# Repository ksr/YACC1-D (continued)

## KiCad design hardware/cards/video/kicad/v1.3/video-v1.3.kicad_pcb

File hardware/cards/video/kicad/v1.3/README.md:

# video-v1.3 — KiCad design for the video card

**Superseded by `../v2.0/` (2026-10-22), which builds on it; kept as the DOTS-jumper design. Not ordered.**

(Was the master from 2026-10-22.) v1.3 is `../v1.2/` (the bench state of 2026-10-21) with one
jumper that chooses **6 or 8 dots a character**, and a new board: **4 layers, routed from scratch** - In1.Cu a solid GND
plane, In2.Cu a solid VCC plane, every signal routed anew, GND and VCC never routed (every power pin is a through-hole
pad on its plane). The outline, the bus connector X1 and the placement are v1.2's; the parts v1.3 adds sit beside IC28.
`tools/eagle_to_kicad_all.py` never writes here (`MASTER` marker file). `./build.sh` rebuilds the board and every report
and checks them (needs KiCad 10 and Freerouting 1.9).

## The two modes

One 12 MHz crystal (Q2, SV4 on 1-2) serves both:

| DOTS jumper (JP2) | IC28 divides by | character clock | screen | 6845 R0..R9 | dots across | EPROM time a character |
|---|---|---|---|---|---|---|
| open (R15 pulls DOTS high) | 6 | 2.0 MHz | **80 x 24** | 126, 80, 98, 10, 31, 6, 24, 27, 0, 7 | 480 | 500 ns |
| fitted (DOTS to GND) | 8 | 1.5 MHz | **64 x 24** | 94, 64, 75, 8, 31, 6, 24, 27, 0, 7 | 512 | 667 ns |

Both 15.75 kHz / 60 Hz. The 64 x 24 table is the one proven on a TV-rate monitor on 2026-10-21 (9 MHz / 6 = the same
1.5 MHz); the 80 x 24 table is centred in that monitor's measured visible window (about 10.3-58.3 us after the sync
starts: the text runs 14.5-54.5 us). `python3 tools/vidsim.py testcard --card v1.3 --dots 6|8 --png card.png` draws
each mode; `vidsim.py chargen --card v1.3` writes the EPROM (`firmware/video/chargen-v13.bin`).

## Changes since v1.2 (schematic)

| # | Change | Pins |
|---|---|---|
| 1 | **IC28 (74163) divides by 16 - P, loading P on its carry** | -CLR (1) to VCC; data A (3) GND, B (4) **DOTS**, C (5) GND, D (6) VCC: P = 8 (/8) or 10 (/6); -LOAD (9) = CHARCLOCK; RCO (15) = net `RCO`; QA (14) unconnected; ENT/ENP (10, 7) stay on N$73 (R10). CRTCCLOCK stays QC (12) -> IC17 21 |
| 2 | **CHARCLOCK = NOT RCO** | IC19/C both inputs (9, 10) on `RCO` (were QA and CRTCCLOCK): one dot low at count 15 in both modes, the same pulse the 74LS166 load and IC22/IC23 get in v1.2 |
| 3 | **DOTS jumper JP2** (2-pin header, silk "DOTS: ON=8") + **R15 4.7k** pull-up | JP2 1 = DOTS, 2 = GND; R15 VCC - DOTS. Fitted = 8 dots, open = 6 dots |
| 4 | **Font select: DOTS on EPROM A10** | IC25 pin 19 (was GND): the 8-dot font at $000, the 6-dot font at $400; A9, A11 stay GND |
| 5 | **DOTS readable at `$D801` bit 0** | latch IC2 1D (pin 3) on DOTS (was JP1 pin 1, now unconnected): 1 = 6 dots, 0 = 8. IC2 LE (pin 11) to VCC (was JP1 pin 13, which floated): the latch is transparent by design; JP1 pin 13 unconnected |
| 5a | **Card ID at `$D801` bit 2** (2026-10-22) | latch IC2 3D (pin 7) to GND (was JP1 pin 4, now unconnected, no-connect flag): bit 2 = 0 says "V1.3" to `ROM 2026-10-22` and later, which then reads DOTS on bit 0 for 80 x 24 or 64 x 24; the V1.0-V1.2 card reads bit 2 = 1 (a jumper on its JP1 3-4) and keeps its 11.0592 MHz table |
| 6 | **IC24 (74LS166) loads all eight bits** | A, B, C (2, 3, 4; were GND) to EPROM O0, O1, O2 (IC25 9, 10, 11) on nets `CG0..CG2`. In 6-dot mode the next load comes after 6 shifts, so only O7..O2 are seen |
| 7 | values, title | Q2 **12MHz**; IC25 **2732 (chargen-v13)**; silkscreen "YACC1 Video Card V1.3" |

Unchanged from v1.2: RS on ADDR1, LPSTB to GND, the R13 / R14 4.7k pull-ups, E without the one-shot (IC1 pin 2 on VCC).
Characters stay 8 scan lines tall in both modes (R9 = 7): taller ones need RA3 to the EPROM and would break the
proposed graphics overlay's 8-plane addressing (`BACKLOG.md`).

**The 6845's clock in 6-dot mode.** QC over counts 10..15 is low for 2 dots and high for 4: **167 ns low / 333 ns high**
at 12 MHz (8-dot mode: 333 / 333 ns). Motorola's MC6845 data sheet gives a minimum clock pulse width of 160 ns low and
200 ns high (**To verify:** from the data sheet as remembered - the tree's `docs/BYTE 6845.pdf` is a scan without the
timing table). 167 ns against 160 ns is a margin of only 7 ns. Fit a faster grade (MC68A45 / MC68B45, or an HD6845S) for
the 6-dot mode, or check the fitted part's sheet; 8-dot mode has ample margin. The ROM's support (read `$D801` bit 0 at
reset, pick 80 or 64 columns and the table) is the next step (`BACKLOG.md`, "Video v1.3").

**The EPROM in 6-dot mode** gets 500 ns a character; the MBM2732A is a 450 ns part: it works with little slack. A faster
part (a 2732A-25, or a 27C32/2764 at 250 ns with a socket adapter) removes the worry.

## The board

| | |
|---|---|
| Layers | 4, 1.6 mm (JLCPCB-style 4-layer): F.Cu signals, **In1.Cu GND plane**, **In2.Cu VCC plane**, B.Cu signals |
| Rules (`video-v1.3.kicad_dru`, the project's net classes) | as the memory card v2.0: signal tracks 0.25 mm, clearance 0.2 mm, vias 0.8 / 0.4 mm, copper to edge 0.5 mm; plane antipads 0.3 mm, thermal reliefs 0.4 mm gap / 0.5 mm spokes; class Power = GND, VCC: not routed |
| Outline, X1, placement | v1.2's (177.8 x 114.0 mm); **JP2** at (179.7, 116.6), pads horizontal, right of IC28; **R15** vertical at x = 185.4 (pads at y 113.0 / 120.62); the "DOTS: ON=8" label below JP2 |
| Route | Freerouting 1.9 on a 2-signal-layer copy (planes dropped, `-inc Power`), one run per DSN component order (seeds 0-7, in parallel), the best kept: **seed 7: 0 unrouted, 39 vias, 8.41 m of 0.25 mm track** (F.Cu 4.29 m, B.Cu 4.13 m; rebuilt 2026-10-22 with the card ID). The other seeds: 39-52 vias, seed 1 with 3 clearance findings |
| Planes | each one solid piece (GND 17,737 mm², VCC 17,724 mm² of the 20,270 mm² board; the rest antipads), plus a few 0.8 mm² slivers between X1's pins |

## Proof

- Schematic vs board (`tools/kicad/compare_netlists.py`): **MATCH, 115/115 nets** (116 before the card ID: N$13 is gone).
- DRC: **0 unconnected** (every GND/VCC pad reaches its net through its plane only: the planes connect), no clearance,
  short or dangling-track finding; the residue is v1.2's cosmetic set, unchanged by type and count: silk_over_copper
  199, silk_overlap 15, silk_edge_clearance 8, lib_footprint_mismatch 3, items_not_allowed 2 (X1's mounting holes in
  X1's own keepout), text_height 2. Schematic parity: footprint_symbol_mismatch 16 and net_conflict 29, the conversion's
  inherited value texts and its "unconnected-(...)" pins, as v1.2; the three net_conflict items v1.2 lacks are the pins
  v1.3 leaves unconnected (IC28 14, JP1 1, JP1 4, JP1 13), and v1.2's for IC28 15 and IC25 9-11 are gone (now used).
- ERC: endpoint_off_grid 35, isolated_pin_label 56, pin_to_pin 9 - v1.2's cosmetic set, unchanged.
- `gen_v13.py verify`: every change above checked pin by pin in the schematic netlist **and** on the board's pads; no
  track on GND or VCC; copper layers F.Cu, In1.Cu, In2.Cu, B.Cu; one plane each.

## Files

| File | What it is |
|---|---|
| `video-v1.3.kicad_pro`, `video-v1.3.kicad_dru` | project and rules (written by `gen_v13.py project`) |
| `video-v1.3.kicad_sch` + `-sheet1/2` | schematic (two sheets, as the Eagle original) |
| `video-v1.3.kicad_pcb` | the 4-layer board (written by `build.sh`) |
| `video-v1.3-eagle.kicad_sym`, `video-v1.3-eagle.pretty/` | project libraries; v1.3 adds the symbol `con-lstb_MA02-1` and KiCad's `PinHeader_1x02_P2.54mm_Vertical` footprint |
| `gen_v13.py`, `build.sh` | the board generator (project, board, dsn, shuffle, ses, stats, silk, verify) and the build |
| `reports/` | netlist + `netlist-compare.txt` (proof), `erc.json`, `drc.json`, schematic PDF, top/bottom renders |

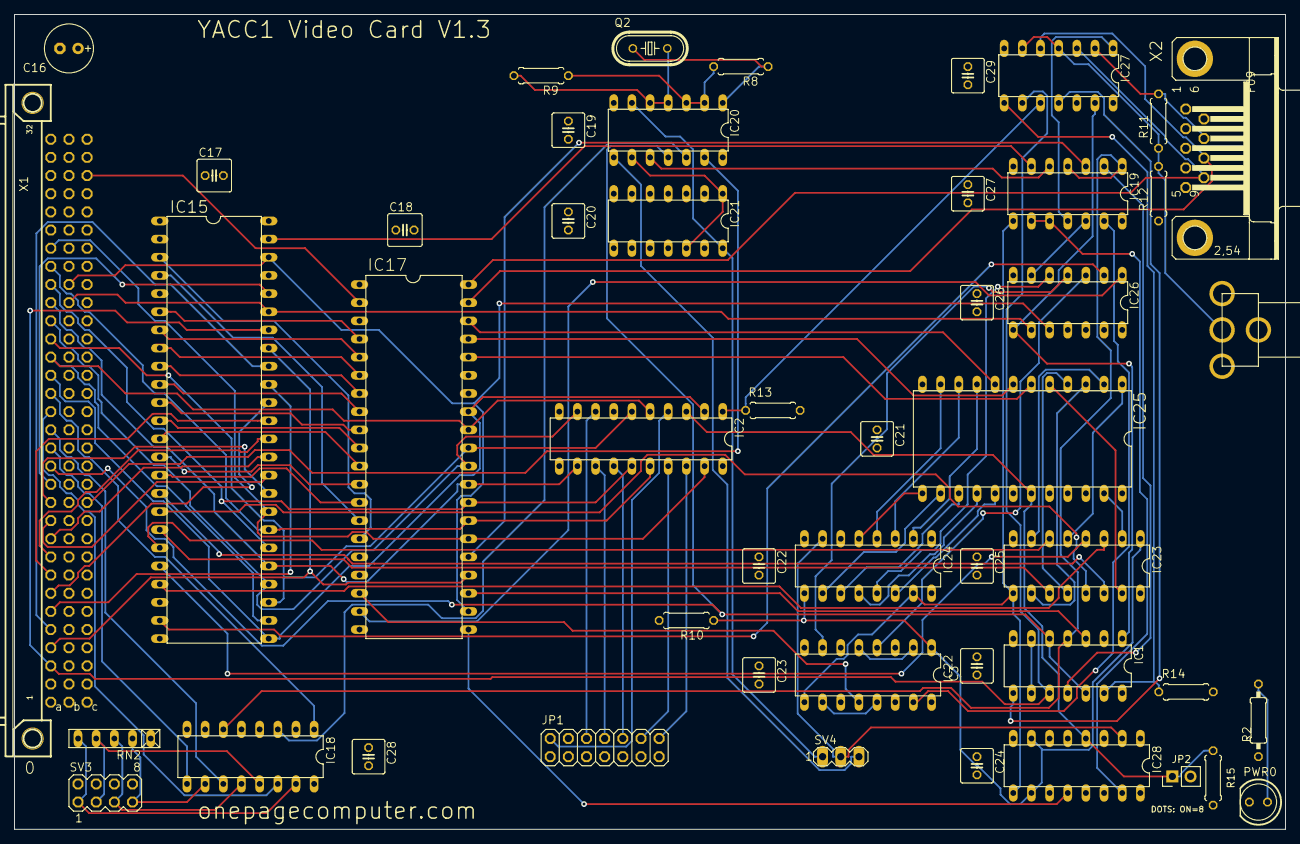
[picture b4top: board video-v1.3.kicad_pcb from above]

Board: 4 copper layers, 177.8 x 114.0 mm, 49 parts (0 on the bottom side), 115 nets.

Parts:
C3, C17, C18, C19, C20, C21, C22, C23, C24, C25, C26, C27, C28, C29: .1; C025-050X050
C16: 10.0; E2,5-7
IC1: 74ALS08N; DIL14
IC2: 74LS373N; DIL20
IC15: VRAM; DIL48
IC17: 6845; DIL40
IC18: 74S85N; DIL16
IC19: 74LS00N; DIL14
IC20: 74LS04N; DIL14
IC21: 74LS90N; DIL14
IC22: 74LS175N; DIL16
IC23: 74LS174N; DIL16
IC24: 74LS166N; DIL16
IC25: 2732 (chargen-v13); DIL24
IC26: 74LS86N; DIL14
IC27: 7416N; DIL14
IC28: 74163; DIL16
JP1: PINHD-2X7; 2X07
JP2: DOTS 8=ON; PinHeader_1x02_P2.54mm_Vertical
PWR0: LED5MM
Q2: 12MHz; HC49U-V
R2: 330; 0207_10
R8, R9, R10: 1K; 0207_7
R11: 33; 0207_7
R12: 270; 0207_7
R13, R14, R15: 4.7K; 0207_7
RN2: RN-5
SV3: MA04-2
SV4: MA03-1
U$3: RCA
X1: FABC96R
X2: F09HP

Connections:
-MEM-RD: IC15.43, IC26.9, X1.B23
-MEM-WR: IC15.46, IC17.22, IC26.10, X1.B24
-RESET: IC17.2, X1.C30
-VMA: IC20.13, X1.C12
ADDR0: IC1.10, IC15.42, IC27.9, X1.A3
ADDR1: IC15.41, IC17.24, X1.A4
ADDR2: IC15.40, X1.A5
ADDR3: IC15.39, X1.A6
ADDR4: IC15.38, X1.A7
ADDR5: IC15.37, X1.A8
ADDR6: IC15.36, X1.A9
ADDR7: IC15.35, X1.A10
ADDR8: IC15.34, X1.A11
ADDR9: IC15.33, X1.A12
ADDR10: IC15.44, X1.A13
ADDR11: IC1.5, IC1.12, IC20.11, X1.A14
ADDR12: IC18.9, X1.A15
ADDR13: IC18.11, X1.A16
ADDR14: IC18.14, X1.A17
ADDR15: IC18.1, X1.A18
BOARDSEL: IC1.4, IC18.6, IC19.1, IC19.4
CG0: IC24.2, IC25.9
CG1: IC24.3, IC25.10
CG2: IC24.4, IC25.11
CHARCLOCK: IC19.8, IC22.9, IC23.9, IC24.15, IC28.9
CLK: IC1.3, IC17.23
CRTCCLOCK: IC17.21, IC28.12
DATA0: IC2.2, IC15.25, IC17.33, X1.A19
DATA1: IC2.5, IC15.26, IC17.32, X1.A20
DATA2: IC2.6, IC15.27, IC17.31, X1.A21
DATA3: IC2.9, IC15.28, IC17.30, X1.A22
DATA4: IC2.12, IC15.29, IC17.29, X1.A23
DATA5: IC2.15, IC15.30, IC17.28, X1.A24
DATA6: IC2.16, IC15.31, IC17.27, X1.A25
DATA7: IC2.19, IC15.32, IC17.26, X1.A26
DOTCLOCK: IC24.7, IC28.2, SV4.2
DOTS: IC2.3, IC25.19, IC28.4, JP2.1, R15.2
GND: C3.2, C16.-, C17.2, C18.2, C19.2, C20.2, C21.2, C22.2, C23.2, C24.2, C25.2, C26.2, C27.2, C28.2, C29.2, IC1.7, IC2.7, IC2.10, IC15.1, IC15.5, IC15.24, IC15.45, IC17.1, IC17.3, IC18.2, IC18.4, IC18.8, IC19.7, IC20.7, IC21.2, IC21.3, IC21.6, IC21.7, IC21.10, IC22.8, IC23.8, IC24.1, IC24.6, IC24.8, IC25.12, IC25.18, IC25.20, IC25.21, IC25.22, IC26.7, IC26.12, IC26.13, IC27.7, IC28.3, IC28.5, IC28.8, JP1.5, JP2.2, PWR0.K, SV3.2, SV3.4, SV3.6, SV3.8, U$3.S1, U$3.S2, U$3.S3, X1.A1, X1.A32, X1.B1, X1.B32, X1.C1, X1.C32, X2.1
unnamed: IC1.1, IC26.8, IC27.13
unnamed: IC1.11, IC19.2
unnamed: IC1.13, IC27.8, R14.1
unnamed: IC1.8, IC27.11
unnamed: IC2.18, JP1.14
unnamed: IC2.17, JP1.12
unnamed: IC2.14, JP1.10
unnamed: IC2.13, JP1.8
unnamed: PWR0.A, R2.1
unnamed: IC2.8, JP1.6
unnamed: IC2.4, JP1.2
unnamed: IC2.1, IC27.10, R13.1
unnamed: IC1.6, IC1.9
unnamed: IC18.10, RN2.2, SV3.7
unnamed: IC18.12, RN2.3, SV3.5
unnamed: IC18.13, RN2.4, SV3.3
unnamed: IC18.15, RN2.5, SV3.1
unnamed: IC15.47, IC19.6
unnamed: IC20.1, Q2.1, R8.1
unnamed: IC20.4, IC20.5, Q2.2, R9.2
unnamed: IC20.2, IC20.3, R8.2, R9.1
unnamed: IC20.6, IC21.14, SV4.1
unnamed: IC20.9, IC21.1, IC21.12
unnamed: IC20.8, SV4.3
unnamed: IC22.2, IC22.5
unnamed: IC24.5, IC25.13
unnamed: IC24.10, IC25.14
unnamed: IC24.11, IC25.15
unnamed: IC24.12, IC25.16
unnamed: IC24.14, IC25.17
unnamed: IC23.2, IC25.23
unnamed: IC23.5, IC25.1
unnamed: IC23.7, IC25.2
unnamed: IC23.10, IC25.3
unnamed: IC23.12, IC25.4
unnamed: IC23.15, IC25.5
unnamed: IC22.1, IC23.1, IC24.9, IC28.7, IC28.10, R10.1
unnamed: IC17.19, IC26.1
unnamed: IC22.4, IC26.3
unnamed: IC22.7, IC26.4
unnamed: IC24.13, IC26.5
unnamed: IC22.10, IC22.13
unnamed: IC17.18, IC22.12
unnamed: IC19.12, IC26.6
unnamed: IC19.13, IC22.15
unnamed: IC17.40, IC27.3, X2.9
unnamed: IC17.39, IC27.5, X2.8
unnamed: IC19.11, IC27.1
unnamed: IC27.4, IC27.6, R11.1, R12.2, U$3.C1
unnamed: IC27.2, R11.2, X2.7
unnamed: IC19.5, IC20.10
unnamed: IC18.3, IC20.12
unnamed: IC17.25, IC19.3
RCO: IC19.9, IC19.10, IC28.15
VADDR0: IC15.6, IC17.4
VADDR1: IC15.7, IC17.5
VADDR2: IC15.8, IC17.6
VADDR3: IC15.9, IC17.7
VADDR4: IC15.10, IC17.8
VADDR5: IC15.11, IC17.9
VADDR6: IC15.12, IC17.10
VADDR7: IC15.13, IC17.11
VADDR8: IC15.14, IC17.12
VADDR9: IC15.15, IC17.13
VADDR10: IC15.4, IC17.14
VADDR11: IC15.3, IC17.15
VCC: C3.1, C16.+, C17.1, C18.1, C19.1, C20.1, C21.1, C22.1, C23.1, C24.1, C25.1, C26.1, C27.1, C28.1, C29.1, IC1.2, IC1.14, IC2.11, IC2.20, IC15.2, IC15.48, IC17.20, IC18.16, IC19.14, IC20.14, IC21.5, IC22.16, IC23.16, IC24.16, IC25.24, IC26.14, IC27.14, IC28.1, IC28.6, IC28.16, JP1.3, R2.2, R10.2, R12.1, R13.2, R14.2, R15.1, RN2.1, X1.A2, X1.A31, X1.B2, X1.B31, X1.C2, X1.C31
VDATA0: IC15.16, IC23.14
VDATA1: IC15.17, IC23.13
VDATA2: IC15.18, IC23.11
VDATA3: IC15.19, IC23.6
VDATA4: IC15.20, IC23.4
VDATA5: IC15.21, IC23.3
VDATA7: IC15.23, IC26.2
VROWS0: IC17.38, IC25.8
VROWS1: IC17.37, IC25.7
VROWS2: IC17.36, IC25.6

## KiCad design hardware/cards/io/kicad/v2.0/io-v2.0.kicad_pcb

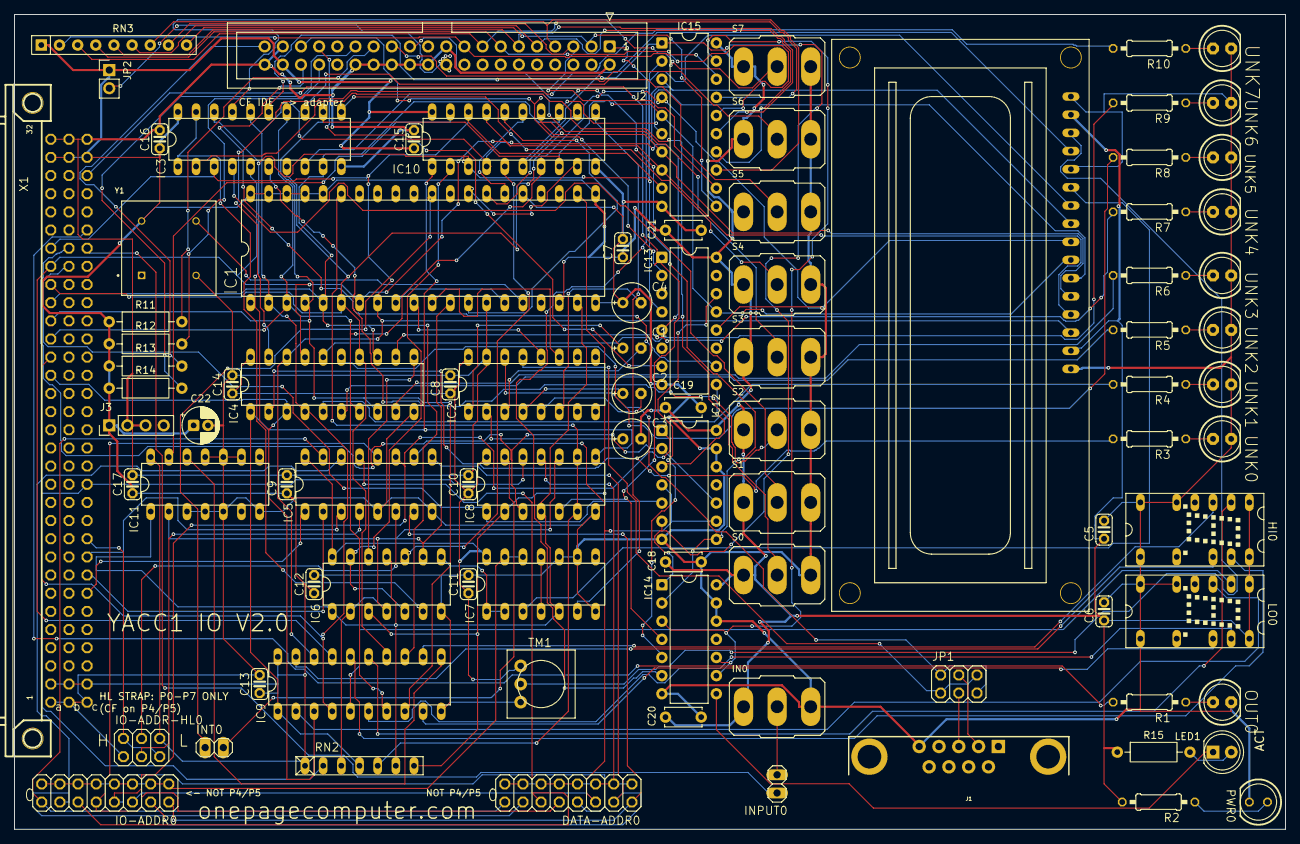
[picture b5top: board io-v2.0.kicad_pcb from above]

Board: 2 copper layers, 177.8 x 114.0 mm, 90 parts (0 on the bottom side), 128 nets.

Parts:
C1, C2, C3, C4: E2,5-6E
C5, C6, C7, C8, C9, C10, C11, C12, C13, C14, C15, C16, C17: C025-024X044
C18, C19, C20, C21: 100n; C_Disc_D5.0mm_W2.5mm_P5.00mm
C22: 10u; CP_Radial_D5.0mm_P2.00mm
DATA-ADDR0: 2X08
HI0: HTIL311A
IC1: DIL40
IC2: MAX232; DIL16
IC3: 74LS244N; DIL20
IC4, IC9, IC10: 74273N; DIL20
IC5: 74LS138N; DIL16
IC6, IC11: 74LS10N; DIL14
IC7: 74LS00N; DIL14
IC8: 74LS06N; DIL14
IC12: 74LS32; DIP-14_W7.62mm
IC13: 74LS175; DIP-16_W7.62mm
IC14: 74LS08; DIP-14_W7.62mm
IC15: 74LS245; DIP-20_W7.62mm
IN0: M9040P
INPUT0: 1X02
INT0: 1X02
IO-ADDR0: 2X08
IO-ADDR-HL0: 2X03
J1: DB9
J2: IDE 40; IDC-Header_2x20_P2.54mm_Vertical
J3: POWER; PinHeader_1x04_P2.54mm_Vertical
JP1: PINHD-2X3; 2X03
JP2: PIN20 5V; PinHeader_1x02_P2.54mm_Vertical
LED1: ACT yellow; LED_D5.0mm
LO0: HTIL311A
OUT0: LED5MM
PWR0: LED5MM
R1, R3, R4, R5, R6, R7, R8, R9, R10: 0207_10
R2: 330; 0207_10
R11, R12, R13, R14: 10k; R_Axial_DIN0207_L6.3mm_D2.5mm_P10.16mm_Horizontal
R15: 1k; R_Axial_DIN0207_L6.3mm_D2.5mm_P10.16mm_Horizontal
RN2: RN-7
RN3: 10k x8; R_Array_SIP9
S0, S1, S2, S3, S4, S5, S6, S7: M9040P
TM1: 10k; TRIM-3386
UNK0, UNK1, UNK2, UNK3, UNK4, UNK5, UNK6, UNK7: LED5MM
X1: FABC96R
X2: HD44780LCD-1602; LCD1602
Y1: ECS-2100AX-200

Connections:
-B-RESET: IC4.1, IC8.8, IC9.1, IC10.1, RN2.4
-INT: IC8.12, RN2.2, X1.C13
-IO-RD: IC8.1, IC12.5, X1.B25
-IO-SEL4: DATA-ADDR0.8, IC5.11, IC12.1, IO-ADDR0.8
-IO-SEL5: DATA-ADDR0.6, IC5.10, IC12.4, IC12.9, IO-ADDR0.6
-IO-WR: IC8.3, IC12.2, IC12.10, X1.B26
-RESET: IC8.5, IC13.1, IC14.4, X1.C30
/Sheet 2/ICLK: IC1.9, IC1.15
/Sheet 2/RX: IC1.10, IC2.12
/Sheet 2/RX-IN: IC2.13, JP1.1, JP1.6
/Sheet 2/TX-OUT: IC2.14, JP1.2, JP1.5
/Sheet 5/-IO-ADDRSEL: IC7.12, IC7.13, IO-ADDR0.1, IO-ADDR0.3, IO-ADDR0.5, IO-ADDR0.7, IO-ADDR0.9, IO-ADDR0.11, IO-ADDR0.13, IO-ADDR0.15
/Sheet 5/-IO-DATASEL: DATA-ADDR0.1, DATA-ADDR0.3, DATA-ADDR0.5, DATA-ADDR0.7, DATA-ADDR0.9, DATA-ADDR0.11, DATA-ADDR0.13, DATA-ADDR0.15, IC8.11
/Sheet 5/-IO-SEL0: DATA-ADDR0.16, IC5.15, IO-ADDR0.16
/Sheet 5/-IO-SEL1: DATA-ADDR0.14, IC5.14, IO-ADDR0.14
/Sheet 5/-IO-SEL2: DATA-ADDR0.12, IC5.13, IO-ADDR0.12
/Sheet 5/-IO-SEL3: DATA-ADDR0.10, IC5.12, IO-ADDR0.10
/Sheet 5/-IO-SEL6: DATA-ADDR0.4, IC5.9, IO-ADDR0.4
/Sheet 5/-IO-SEL7: DATA-ADDR0.2, IC5.7, IO-ADDR0.2
/Sheet 7/-CFOE: IC14.3, IC14.9, IC14.10, IC15.19
/Sheet 7/-CFRESET: IC14.6, J2.1
/Sheet 7/-DASP: J2.39, R13.2
/Sheet 7/-DMACK: J2.29, R14.2
/Sheet 7/-IOR: IC12.6, IC14.1, IC15.1, J2.25
/Sheet 7/-IOW: IC12.8, IC14.2, J2.23
/Sheet 7/-PDIAG: J2.34, R12.2
/Sheet 7/-SRST: IC13.14, IC14.5
/Sheet 7/ACTK: IC14.8, LED1.1
/Sheet 7/CFD0: IC15.18, J2.17, RN3.2
/Sheet 7/CFD1: IC15.17, J2.15, RN3.3
/Sheet 7/CFD2: IC15.16, J2.13, RN3.4
/Sheet 7/CFD3: IC15.15, J2.11, RN3.5
/Sheet 7/CFD4: IC15.14, J2.9, RN3.6
/Sheet 7/CFD5: IC15.13, J2.7, RN3.7
/Sheet 7/CFD6: IC15.12, J2.5, RN3.8
/Sheet 7/CFD7: IC15.11, J2.3, RN3.9
/Sheet 7/DA0: IC13.2, J2.35
/Sheet 7/DA1: IC13.7, J2.33
/Sheet 7/DA2: IC13.10, J2.36
/Sheet 7/IORDY: J2.27, R11.2
/Sheet 7/LATCHCLK: IC12.3, IC13.9
/Sheet 7/LEDA2: LED1.2, R15.2
/Sheet 7/PIN20: J2.20, JP2.2
DATA0: IC1.1, IC3.18, IC4.3, IC9.3, IC10.3, IC13.4, IC15.2, X1.A19, X2.7
DATA1: IC1.2, IC3.16, IC4.4, IC9.4, IC10.4, IC13.5, IC15.3, X1.A20, X2.8
DATA2: IC1.3, IC3.14, IC4.7, IC9.7, IC10.7, IC13.12, IC15.4, X1.A21, X2.9
DATA3: IC1.4, IC3.12, IC4.8, IC9.8, IC10.8, IC13.13, IC15.5, X1.A22, X2.10
DATA4: IC1.5, IC3.9, IC4.13, IC9.13, IC10.13, IC15.6, X1.A23, X2.11
DATA5: IC1.6, IC3.7, IC4.14, IC9.14, IC10.14, IC15.7, X1.A24, X2.12
DATA6: IC1.7, IC3.5, IC4.17, IC9.17, IC10.17, IC15.8, X1.A25, X2.13
DATA7: IC1.8, IC3.3, IC4.18, IC9.18, IC10.18, IC15.9, X1.A26, X2.14
GND: C4.+, C5.2, C6.2, C7.2, C8.2, C9.2, C10.2, C11.2, C12.2, C13.2, C14.2, C15.2, C16.2, C17.2, C18.2, C19.2, C20.2, C21.2, C22.2, HI0.5, HI0.7, HI0.8, IC1.14, IC1.20, IC1.25, IC2.15, IC3.10, IC4.10, IC5.5, IC5.8, IC6.7, IC7.7, IC7.9, IC7.10, IC8.7, IC9.10, IC10.10, IC11.3, IC11.4, IC11.5, IC11.7, IC11.9, IC11.10, IC11.11, IC12.7, IC12.12, IC12.13, IC13.8, IC14.7, IC14.12, IC14.13, IC15.10, IN0.3, IO-ADDR-HL0.1, J1.5, J2.2, J2.19, J2.22, J2.24, J2.26, J2.28, J2.30, J2.37, J2.40, J3.2, J3.3, LO0.5, LO0.7, LO0.8, OUT0.K, PWR0.K, S0.3, S1.3, S2.3, S3.3, S4.3, S5.3, S6.3, S7.3, TM1.3, UNK0.K, UNK1.K, UNK2.K, UNK3.K, UNK4.K, UNK5.K, UNK6.K, UNK7.K, X1.A1, X1.A32, X1.B1, X1.B32, X1.C1, X1.C32, X2.1, X2.5, X2.16, Y1.4
IN: INPUT0.1, X1.C26
IO-ADDR0: IC5.1, X1.C7
IO-ADDR1: IC5.2, X1.C8
IO-ADDR2: IC5.3, X1.C9
IO-ADDR3: IO-ADDR-HL0.2, IO-ADDR-HL0.5, X1.C10
IO-RD: IC1.22, IC6.3, IC8.2, RN2.7
IO-SELDATA: IC1.12, IC6.2, IC6.4, IC6.9, IC8.10, IC11.2, RN2.3
IO-WR: IC1.19, IC6.1, IC6.11, IC7.5, IC8.4, IC11.1, RN2.6
LCD-ENABLE: IC6.10, IC10.5
LCD-REGISTER: IC10.6, X2.4
unnamed: HI0.3, IC9.12
unnamed: HI0.2, IC9.15
unnamed: HI0.13, IC9.16
unnamed: HI0.12, IC9.19
unnamed: IC1.30, INT0.1
unnamed: IC1.11, IC2.11
unnamed: IC1.16, Y1.5
unnamed: C1.+, IC2.1
unnamed: C1.-, IC2.3
unnamed: C2.+, IC2.4
unnamed: C2.-, IC2.5
unnamed: C3.+, IC2.2
unnamed: C4.-, IC2.6
unnamed: IC3.2, S0.2
unnamed: IC3.4, S1.2
unnamed: IC3.6, S2.2
unnamed: IC3.8, S3.2
unnamed: IC3.1, IC3.19, IC6.6
unnamed: IC3.11, S4.2
unnamed: IC3.13, S5.2
unnamed: IC3.15, S6.2
unnamed: IC3.17, S7.2
unnamed: IC4.11, IC6.12
unnamed: IC4.2, R3.2
unnamed: IC4.5, R4.2
unnamed: IC4.6, R5.2
unnamed: IC4.9, R6.2
unnamed: IC4.12, R7.2
unnamed: IC4.15, R8.2
unnamed: IC4.16, R9.2
unnamed: IC4.19, R10.2
unnamed: IC5.6, IO-ADDR-HL0.4
unnamed: IC5.4, IO-ADDR-HL0.3
unnamed: IC6.8, IC7.1, IC7.2
unnamed: IC7.3, X2.6
unnamed: IC7.4, IC7.11
unnamed: IC8.13, INT0.2
unnamed: IC9.2, LO0.3
unnamed: IC9.5, LO0.2
unnamed: IC9.6, LO0.13
unnamed: IC9.9, LO0.12
unnamed: IC7.6, IC10.11
unnamed: IC9.11, IC11.12
unnamed: IN0.2, INPUT0.2
unnamed: J1.2, JP1.4
unnamed: J1.3, JP1.3
unnamed: OUT0.A, R1.1
unnamed: PWR0.A, R2.1
unnamed: R3.1, UNK0.A
unnamed: R4.1, UNK1.A
unnamed: R5.1, UNK2.A
unnamed: R6.1, UNK3.A
unnamed: R7.1, UNK4.A
unnamed: R8.1, UNK5.A
unnamed: R9.1, UNK6.A
unnamed: R10.1, UNK7.A
unnamed: TM1.2, X2.3
OUT: R1.2, X1.C27
RESET: IC1.35, IC8.6, IC8.9, RN2.5
SWITCH-LED: IC6.5, IC6.13, IC10.2
TIL311: IC10.19, IC11.13
UART-A0: IC1.28, IC10.9
UART-A1: IC1.27, IC10.12
UART-A2: IC1.26, IC10.15
UART-CS: IC1.13, IC10.16
VCC: C3.-, C5.1, C6.1, C7.1, C8.1, C9.1, C10.1, C11.1, C12.1, C13.1, C14.1, C15.1, C16.1, C17.1, C18.1, C19.1, C20.1, C21.1, C22.1, HI0.1, HI0.14, IC1.18, IC1.21, IC1.36, IC1.37, IC1.38, IC1.39, IC1.40, IC2.16, IC3.20, IC4.20, IC5.16, IC6.14, IC7.14, IC8.14, IC9.20, IC10.20, IC11.14, IC12.14, IC13.16, IC14.14, IC15.20, IN0.1, IO-ADDR-HL0.6, J2.38, J3.1, JP2.1, LO0.1, LO0.14, R2.2, R11.1, R12.1, R13.1, R14.1, R15.1, RN2.1, RN3.1, S0.1, S1.1, S2.1, S3.1, S4.1, S5.1, S6.1, S7.1, TM1.1, X1.A2, X1.A31, X1.B2, X1.B31, X1.C2, X1.C31, X2.2, X2.15, Y1.8

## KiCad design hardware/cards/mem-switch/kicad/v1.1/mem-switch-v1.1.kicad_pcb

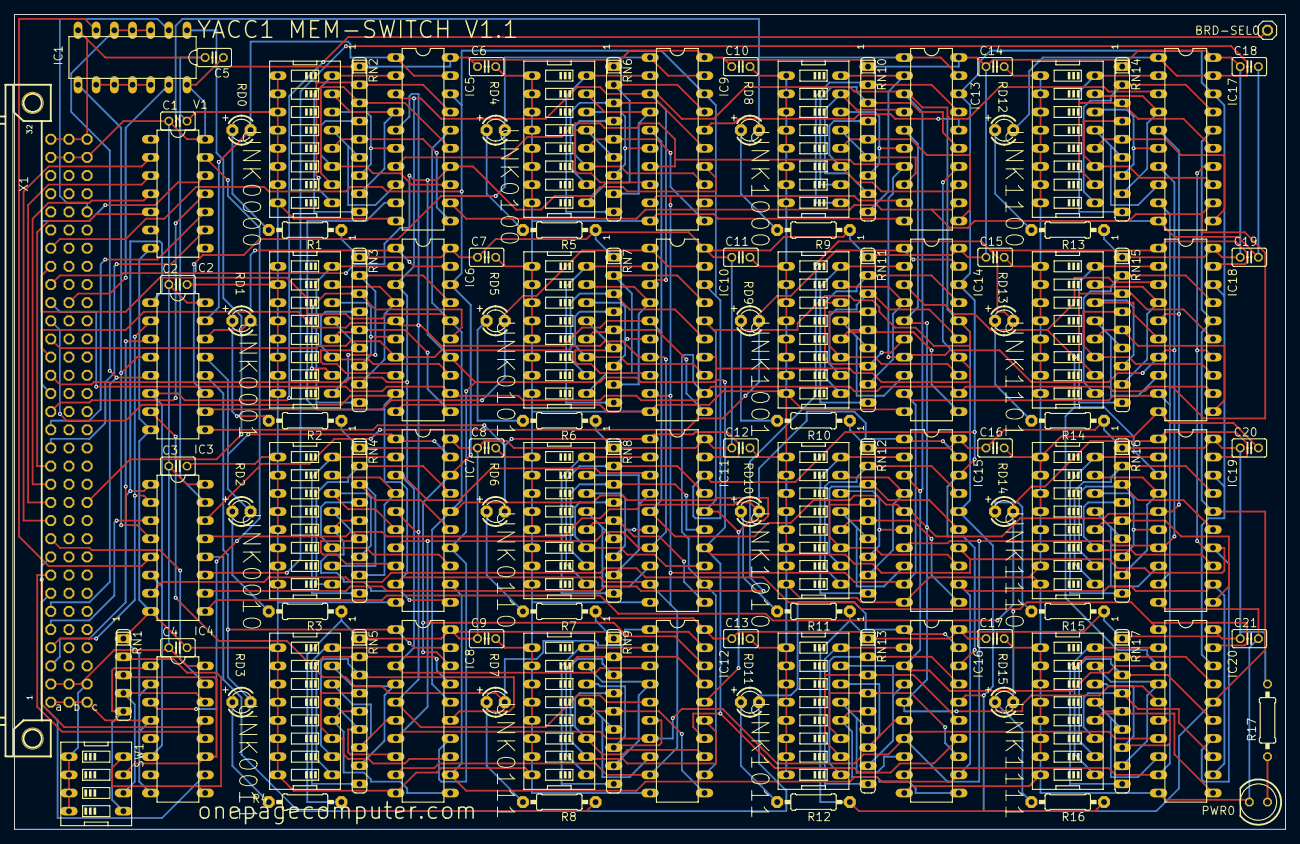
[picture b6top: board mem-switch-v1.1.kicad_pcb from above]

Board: 2 copper layers, 177.8 x 114.0 mm, 112 parts (0 on the bottom side), 199 nets.

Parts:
BRD-SEL0: PINHD-1X1; 1X01
C1, C2, C3, C4, C5, C6, C7, C8, C9, C10, C11, C12, C13, C14, C15, C16, C17, C18, C19, C20, C21: C025-025X050
IC1: 74ALS27N; DIL14
IC2, IC3: 74LS138N; DIL16
IC4: 74LS85N; DIL16
IC5, IC6, IC7, IC8, IC9, IC10, IC11, IC12, IC13, IC14, IC15, IC16, IC17, IC18, IC19, IC20: 74LS244N; DIL20
PWR0: LED5MM
R1, R2, R3, R4, R5, R6, R7, R8, R9, R10, R11, R12, R13, R14, R15, R16: 0207_10
R17: 330; 0207_10
RD0, RD1, RD2, RD3, RD4, RD5, RD6, RD7, RD8, RD9, RD10, RD11, RD12, RD13, RD14, RD15: LED3MM
RN1: SIL5
RN2, RN3, RN4, RN5, RN6, RN7, RN8, RN9, RN10, RN11, RN12, RN13, RN14, RN15, RN16, RN17: SIL9
SW1: EDG-04
UNK0000, UNK0001, UNK0010, UNK0011, UNK0100, UNK0101, UNK0110, UNK0111, UNK1000, UNK1001, UNK1010, UNK1011, UNK1100, UNK1101, UNK1110, UNK1111: EDG-08
V1: 744078N; DIL14
X1: FABC96R

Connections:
-BUS-EN: IC1.2, X1.C28
-MEM-RD: IC1.13, X1.B23
-VMA: IC1.1, X1.C12
ADDR0: IC2.1, IC3.1, X1.A3
ADDR1: IC2.2, IC3.2, X1.A4
ADDR2: IC2.3, IC3.3, X1.A5
ADDR3: IC1.3, IC1.4, IC1.5, IC2.5, X1.A6
ADDR4: IC4.10, X1.A7
ADDR5: IC4.12, X1.A8
ADDR6: IC4.13, X1.A9
ADDR7: IC4.15, X1.A10
ADDR8: V1.2, X1.A11
ADDR9: V1.3, X1.A12
ADDR10: V1.4, X1.A13
ADDR11: V1.5, X1.A14
ADDR12: V1.9, X1.A15
ADDR13: V1.10, X1.A16
ADDR14: V1.11, X1.A17
ADDR15: V1.12, X1.A18
DATA0: IC5.3, IC6.3, IC7.3, IC8.3, IC9.3, IC10.3, IC11.3, IC12.3, IC13.3, IC14.3, IC15.3, IC16.3, IC17.3, IC18.3, IC19.3, IC20.3, X1.A19
DATA1: IC5.5, IC6.5, IC7.5, IC8.5, IC9.5, IC10.5, IC11.5, IC12.5, IC13.5, IC14.5, IC15.5, IC16.5, IC17.5, IC18.5, IC19.5, IC20.5, X1.A20
DATA2: IC5.7, IC6.7, IC7.7, IC8.7, IC9.7, IC10.7, IC11.7, IC12.7, IC13.7, IC14.7, IC15.7, IC16.7, IC17.7, IC18.7, IC19.7, IC20.7, X1.A21
DATA3: IC5.9, IC6.9, IC7.9, IC8.9, IC9.9, IC10.9, IC11.9, IC12.9, IC13.9, IC14.9, IC15.9, IC16.9, IC17.9, IC18.9, IC19.9, IC20.9, X1.A22
DATA4: IC5.12, IC6.12, IC7.12, IC8.12, IC9.12, IC10.12, IC11.12, IC12.12, IC13.12, IC14.12, IC15.12, IC16.12, IC17.12, IC18.12, IC19.12, IC20.12, X1.A23
DATA5: IC5.14, IC6.14, IC7.14, IC8.14, IC9.14, IC10.14, IC11.14, IC12.14, IC13.14, IC14.14, IC15.14, IC16.14, IC17.14, IC18.14, IC19.14, IC20.14, X1.A24
DATA6: IC5.16, IC6.16, IC7.16, IC8.16, IC9.16, IC10.16, IC11.16, IC12.16, IC13.16, IC14.16, IC15.16, IC16.16, IC17.16, IC18.16, IC19.16, IC20.16, X1.A25
DATA7: IC5.18, IC6.18, IC7.18, IC8.18, IC9.18, IC10.18, IC11.18, IC12.18, IC13.18, IC14.18, IC15.18, IC16.18, IC17.18, IC18.18, IC19.18, IC20.18, X1.A26
GND: C1.2, C2.2, C3.2, C4.2, C5.2, C6.2, C7.2, C8.2, C9.2, C10.2, C11.2, C12.2, C13.2, C14.2, C15.2, C16.2, C17.2, C18.2, C19.2, C20.2, C21.2, IC1.7, IC2.8, IC3.8, IC4.2, IC4.4, IC4.8, IC5.10, IC6.10, IC7.10, IC8.10, IC9.10, IC10.10, IC11.10, IC12.10, IC13.10, IC14.10, IC15.10, IC16.10, IC17.10, IC18.10, IC19.10, IC20.10, PWR0.K, RN1.1, UNK0000.9, UNK0000.10, UNK0000.11, UNK0000.12, UNK0000.13, UNK0000.14, UNK0000.15, UNK0000.16, UNK0001.9, UNK0001.10, UNK0001.11, UNK0001.12, UNK0001.13, UNK0001.14, UNK0001.15, UNK0001.16, UNK0010.9, UNK0010.10, UNK0010.11, UNK0010.12, UNK0010.13, UNK0010.14, UNK0010.15, UNK0010.16, UNK0011.9, UNK0011.10, UNK0011.11, UNK0011.12, UNK0011.13, UNK0011.14, UNK0011.15, UNK0011.16, UNK0100.9, UNK0100.10, UNK0100.11, UNK0100.12, UNK0100.13, UNK0100.14, UNK0100.15, UNK0100.16, UNK0101.9, UNK0101.10, UNK0101.11, UNK0101.12, UNK0101.13, UNK0101.14, UNK0101.15, UNK0101.16, UNK0110.9, UNK0110.10, UNK0110.11, UNK0110.12, UNK0110.13, UNK0110.14, UNK0110.15, UNK0110.16, UNK0111.9, UNK0111.10, UNK0111.11, UNK0111.12, UNK0111.13, UNK0111.14, UNK0111.15, UNK0111.16, UNK1000.9, UNK1000.10, UNK1000.11, UNK1000.12, UNK1000.13, UNK1000.14, UNK1000.15, UNK1000.16, UNK1001.9, UNK1001.10, UNK1001.11, UNK1001.12, UNK1001.13, UNK1001.14, UNK1001.15, UNK1001.16, UNK1010.9, UNK1010.10, UNK1010.11, UNK1010.12, UNK1010.13, UNK1010.14, UNK1010.15, UNK1010.16, UNK1011.9, UNK1011.10, UNK1011.11, UNK1011.12, UNK1011.13, UNK1011.14, UNK1011.15, UNK1011.16, UNK1100.9, UNK1100.10, UNK1100.11, UNK1100.12, UNK1100.13, UNK1100.14, UNK1100.15, UNK1100.16, UNK1101.9, UNK1101.10, UNK1101.11, UNK1101.12, UNK1101.13, UNK1101.14, UNK1101.15, UNK1101.16, UNK1110.9, UNK1110.10, UNK1110.11, UNK1110.12, UNK1110.13, UNK1110.14, UNK1110.15, UNK1110.16, UNK1111.9, UNK1111.10, UNK1111.11, UNK1111.12, UNK1111.13, UNK1111.14, UNK1111.15, UNK1111.16, V1.7, X1.A1, X1.A32, X1.B1, X1.B32, X1.C1, X1.C32
unnamed: IC5.17, RN2.2, UNK0000.1
unnamed: IC5.15, RN2.3, UNK0000.2
unnamed: IC5.13, RN2.4, UNK0000.3
unnamed: IC5.11, RN2.5, UNK0000.4
unnamed: IC5.8, RN2.6, UNK0000.5
unnamed: BRD-SEL0.1, IC2.6, IC3.6, IC4.6
unnamed: IC5.6, RN2.7, UNK0000.6
unnamed: IC5.4, RN2.8, UNK0000.7
unnamed: IC5.2, RN2.9, UNK0000.8
unnamed: IC6.17, RN3.2, UNK0001.1
unnamed: PWR0.A, R17.1
unnamed: IC6.15, RN3.3, UNK0001.2
unnamed: IC6.13, RN3.4, UNK0001.3
unnamed: IC6.11, RN3.5, UNK0001.4
unnamed: IC6.8, RN3.6, UNK0001.5
unnamed: IC6.6, RN3.7, UNK0001.6
unnamed: IC6.4, RN3.8, UNK0001.7
unnamed: IC6.2, RN3.9, UNK0001.8
unnamed: IC1.9, IC1.10, IC1.11, IC1.12
unnamed: IC7.17, RN4.2, UNK0010.1
unnamed: IC7.15, RN4.3, UNK0010.2
unnamed: IC7.13, RN4.4, UNK0010.3
unnamed: IC7.11, RN4.5, UNK0010.4
unnamed: IC7.8, RN4.6, UNK0010.5
unnamed: IC7.6, RN4.7, UNK0010.6
unnamed: IC7.4, RN4.8, UNK0010.7
unnamed: IC7.2, RN4.9, UNK0010.8
unnamed: IC4.9, RN1.2, SW1.8
unnamed: IC8.17, RN5.2, UNK0011.1
unnamed: IC8.15, RN5.3, UNK0011.2
unnamed: IC8.13, RN5.4, UNK0011.3
unnamed: IC8.11, RN5.5, UNK0011.4
unnamed: IC8.8, RN5.6, UNK0011.5
unnamed: IC8.6, RN5.7, UNK0011.6
unnamed: IC8.4, RN5.8, UNK0011.7
unnamed: IC8.2, RN5.9, UNK0011.8
unnamed: IC1.6, IC3.5
unnamed: IC9.17, RN6.2, UNK0100.1
unnamed: IC9.15, RN6.3, UNK0100.2
unnamed: IC9.13, RN6.4, UNK0100.3
unnamed: IC9.11, RN6.5, UNK0100.4
unnamed: IC9.8, RN6.6, UNK0100.5
unnamed: IC9.6, RN6.7, UNK0100.6
unnamed: IC9.4, RN6.8, UNK0100.7
unnamed: IC9.2, RN6.9, UNK0100.8
unnamed: IC4.11, RN1.3, SW1.7
unnamed: IC10.17, RN7.2, UNK0101.1
unnamed: IC10.15, RN7.3, UNK0101.2
unnamed: IC10.13, RN7.4, UNK0101.3
unnamed: IC10.11, RN7.5, UNK0101.4
unnamed: IC10.8, RN7.6, UNK0101.5
unnamed: IC10.6, RN7.7, UNK0101.6
unnamed: IC10.4, RN7.8, UNK0101.7
unnamed: IC10.2, RN7.9, UNK0101.8
unnamed: IC4.3, V1.13
unnamed: IC11.17, RN8.2, UNK0110.1
unnamed: IC11.15, RN8.3, UNK0110.2
unnamed: IC11.13, RN8.4, UNK0110.3
unnamed: IC11.11, RN8.5, UNK0110.4
unnamed: IC11.8, RN8.6, UNK0110.5
unnamed: IC11.6, RN8.7, UNK0110.6
unnamed: IC11.4, RN8.8, UNK0110.7
unnamed: IC11.2, RN8.9, UNK0110.8
unnamed: IC4.14, RN1.4, SW1.6
unnamed: IC12.17, RN9.2, UNK0111.1
unnamed: IC12.15, RN9.3, UNK0111.2
unnamed: IC12.13, RN9.4, UNK0111.3
unnamed: IC12.11, RN9.5, UNK0111.4
unnamed: IC12.8, RN9.6, UNK0111.5
unnamed: IC12.6, RN9.7, UNK0111.6
unnamed: IC12.4, RN9.8, UNK0111.7
unnamed: IC12.2, RN9.9, UNK0111.8
unnamed: IC4.1, RN1.5, SW1.5
unnamed: IC13.17, RN10.2, UNK1000.1
unnamed: IC13.15, RN10.3, UNK1000.2
unnamed: IC13.13, RN10.4, UNK1000.3
unnamed: IC13.11, RN10.5, UNK1000.4
unnamed: IC13.8, RN10.6, UNK1000.5
unnamed: IC13.6, RN10.7, UNK1000.6
unnamed: IC13.4, RN10.8, UNK1000.7
unnamed: IC13.2, RN10.9, UNK1000.8
unnamed: IC1.8, IC2.4, IC3.4
unnamed: IC14.17, RN11.2, UNK1001.1
unnamed: IC14.15, RN11.3, UNK1001.2
unnamed: IC14.13, RN11.4, UNK1001.3
unnamed: IC14.11, RN11.5, UNK1001.4
unnamed: IC14.8, RN11.6, UNK1001.5
unnamed: IC14.6, RN11.7, UNK1001.6
unnamed: IC14.4, RN11.8, UNK1001.7
unnamed: IC14.2, RN11.9, UNK1001.8
unnamed: R1.2, RD0.A
unnamed: IC15.17, RN12.2, UNK1010.1
unnamed: IC15.15, RN12.3, UNK1010.2
unnamed: IC15.13, RN12.4, UNK1010.3
unnamed: IC15.11, RN12.5, UNK1010.4
unnamed: IC15.8, RN12.6, UNK1010.5
unnamed: IC15.6, RN12.7, UNK1010.6
unnamed: IC15.4, RN12.8, UNK1010.7
unnamed: IC15.2, RN12.9, UNK1010.8
unnamed: R2.2, RD1.A
unnamed: IC16.17, RN13.2, UNK1011.1
unnamed: IC16.15, RN13.3, UNK1011.2
unnamed: IC16.13, RN13.4, UNK1011.3
unnamed: IC16.11, RN13.5, UNK1011.4
unnamed: IC16.8, RN13.6, UNK1011.5
unnamed: IC16.6, RN13.7, UNK1011.6
unnamed: IC16.4, RN13.8, UNK1011.7
unnamed: IC16.2, RN13.9, UNK1011.8
unnamed: R3.2, RD2.A
unnamed: IC17.17, RN14.2, UNK1100.1
unnamed: IC17.15, RN14.3, UNK1100.2
unnamed: IC17.13, RN14.4, UNK1100.3
unnamed: IC17.11, RN14.5, UNK1100.4
unnamed: IC17.8, RN14.6, UNK1100.5
unnamed: IC17.6, RN14.7, UNK1100.6
unnamed: IC17.4, RN14.8, UNK1100.7
unnamed: IC17.2, RN14.9, UNK1100.8
unnamed: R4.2, RD3.A
unnamed: IC18.17, RN15.2, UNK1101.1
unnamed: IC18.15, RN15.3, UNK1101.2
unnamed: IC18.13, RN15.4, UNK1101.3
unnamed: IC18.11, RN15.5, UNK1101.4
unnamed: IC18.8, RN15.6, UNK1101.5
unnamed: IC18.6, RN15.7, UNK1101.6
unnamed: IC18.4, RN15.8, UNK1101.7
unnamed: IC18.2, RN15.9, UNK1101.8
unnamed: R5.2, RD4.A
unnamed: IC19.17, RN16.2, UNK1110.1
unnamed: IC19.15, RN16.3, UNK1110.2
unnamed: IC19.13, RN16.4, UNK1110.3
unnamed: IC19.11, RN16.5, UNK1110.4
unnamed: IC19.8, RN16.6, UNK1110.5
unnamed: IC19.6, RN16.7, UNK1110.6
unnamed: IC19.4, RN16.8, UNK1110.7
unnamed: IC19.2, RN16.9, UNK1110.8
unnamed: R6.2, RD5.A
unnamed: IC20.17, RN17.2, UNK1111.1
unnamed: IC20.15, RN17.3, UNK1111.2
unnamed: IC20.13, RN17.4, UNK1111.3
unnamed: IC20.11, RN17.5, UNK1111.4
unnamed: IC20.8, RN17.6, UNK1111.5
unnamed: IC20.6, RN17.7, UNK1111.6
unnamed: IC20.4, RN17.8, UNK1111.7
unnamed: IC20.2, RN17.9, UNK1111.8
unnamed: R7.2, RD6.A
unnamed: R8.2, RD7.A
unnamed: R9.2, RD8.A
unnamed: R10.2, RD9.A
unnamed: R11.2, RD10.A
unnamed: R12.2, RD11.A
unnamed: R13.2, RD12.A
unnamed: R14.2, RD13.A
unnamed: R15.2, RD14.A
unnamed: R16.2, RD15.A
SW0: IC2.15, IC5.1, IC5.19, RD0.K
SW1: IC2.14, IC6.1, IC6.19, RD1.K
SW2: IC2.13, IC7.1, IC7.19, RD2.K
SW3: IC2.12, IC8.1, IC8.19, RD3.K
SW4: IC2.11, IC9.1, IC9.19, RD4.K
SW5: IC2.10, IC10.1, IC10.19, RD5.K
SW6: IC2.9, IC11.1, IC11.19, RD6.K
SW7: IC2.7, IC12.1, IC12.19, RD7.K
SW8: IC3.15, IC13.1, IC13.19, RD8.K
SW9: IC3.14, IC14.1, IC14.19, RD9.K
SW10: IC3.13, IC15.1, IC15.19, RD10.K
SW11: IC3.12, IC16.1, IC16.19, RD11.K
SW12: IC3.11, IC17.1, IC17.19, RD12.K
SW13: IC3.10, IC18.1, IC18.19, RD13.K
SW14: IC3.9, IC19.1, IC19.19, RD14.K
SW15: IC3.7, IC20.1, IC20.19, RD15.K
VCC: C1.1, C2.1, C3.1, C4.1, C5.1, C6.1, C7.1, C8.1, C9.1, C10.1, C11.1, C12.1, C13.1, C14.1, C15.1, C16.1, C17.1, C18.1, C19.1, C20.1, C21.1, IC1.14, IC2.16, IC3.16, IC4.16, IC5.20, IC6.20, IC7.20, IC8.20, IC9.20, IC10.20, IC11.20, IC12.20, IC13.20, IC14.20, IC15.20, IC16.20, IC17.20, IC18.20, IC19.20, IC20.20, R1.1, R2.1, R3.1, R4.1, R5.1, R6.1, R7.1, R8.1, R9.1, R10.1, R11.1, R12.1, R13.1, R14.1, R15.1, R16.1, R17.2, RN2.1, RN3.1, RN4.1, RN5.1, RN6.1, RN7.1, RN8.1, RN9.1, RN10.1, RN11.1, RN12.1, RN13.1, RN14.1, RN15.1, RN16.1, RN17.1, SW1.1, SW1.2, SW1.3, SW1.4, V1.14, X1.A2, X1.A31, X1.B2, X1.B31, X1.C2, X1.C31

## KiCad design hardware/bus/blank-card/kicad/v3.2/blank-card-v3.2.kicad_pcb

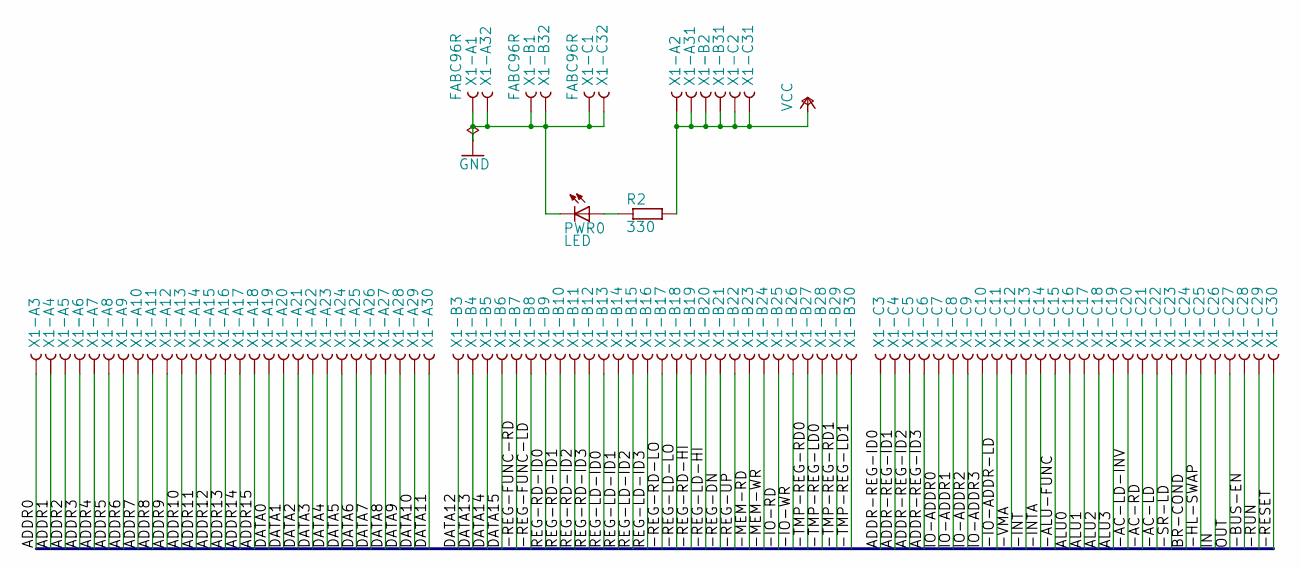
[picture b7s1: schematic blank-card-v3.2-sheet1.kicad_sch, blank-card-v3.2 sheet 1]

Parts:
PWR0: LED; LED5MM
R2: 330; 0207_10
X1: FABC96R

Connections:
-AC-LD: X1.C22
-AC-LD-INV: X1.C20
-AC-RD: X1.C21
-ALU-FUNC: X1.C15
-BUS-EN: X1.C28
-HL-SWAP: X1.C25
-INT: X1.C13
-INTA: X1.C14
-IO-ADDR-LD: X1.C11
-IO-RD: X1.B25
-IO-WR: X1.B26
-MEM-RD: X1.B23
-MEM-WR: X1.B24
-REG-DN: X1.B21
-REG-FUNC-LD: X1.B8
-REG-FUNC-RD: X1.B7
-REG-LD-HI: X1.B20
-REG-LD-LO: X1.B18
-REG-RD-HI: X1.B19
-REG-RD-LO: X1.B17
-REG-UP: X1.B22
-RESET: X1.C30
-RUN: X1.C29
-SR-LD: X1.C23
-TMP-REG-LD0: X1.B28
-TMP-REG-LD1: X1.B30
-TMP-REG-RD0: X1.B27
-TMP-REG-RD1: X1.B29
-VMA: X1.C12
ADDR0: X1.A3
ADDR1: X1.A4
ADDR2: X1.A5
ADDR3: X1.A6
ADDR4: X1.A7
ADDR5: X1.A8
ADDR6: X1.A9
ADDR7: X1.A10
ADDR8: X1.A11
ADDR9: X1.A12
ADDR10: X1.A13
ADDR11: X1.A14
ADDR12: X1.A15
ADDR13: X1.A16
ADDR14: X1.A17
ADDR15: X1.A18
ADDR-REG-ID0: X1.C3
ADDR-REG-ID1: X1.C4
ADDR-REG-ID2: X1.C5
ADDR-REG-ID3: X1.C6
ALU0: X1.C16
ALU1: X1.C17
ALU2: X1.C18
ALU3: X1.C19
BR-COND: X1.C24
DATA0: X1.A19
DATA1: X1.A20
DATA2: X1.A21
DATA3: X1.A22
DATA4: X1.A23
DATA5: X1.A24
DATA6: X1.A25
DATA7: X1.A26
DATA8: X1.A27
DATA9: X1.A28
DATA10: X1.A29
DATA11: X1.A30
DATA12: X1.B3
DATA13: X1.B4
DATA14: X1.B5
DATA15: X1.B6
GND: PWR0.K (C), X1.A1, X1.A32, X1.B1, X1.B32, X1.C1, X1.C32
IN: X1.C26
IO-ADDR0: X1.C7
IO-ADDR1: X1.C8
IO-ADDR2: X1.C9
IO-ADDR3: X1.C10
unnamed: PWR0.A, R2.1
OUT: X1.C27
REG-LD-ID0: X1.B13
REG-LD-ID1: X1.B14
REG-LD-ID2: X1.B15
REG-LD-ID3: X1.B16
REG-RD-ID0: X1.B9
REG-RD-ID1: X1.B10
REG-RD-ID2: X1.B11
REG-RD-ID3: X1.B12
VCC: R2.2, X1.A2, X1.A31, X1.B2, X1.B31, X1.C2, X1.C31

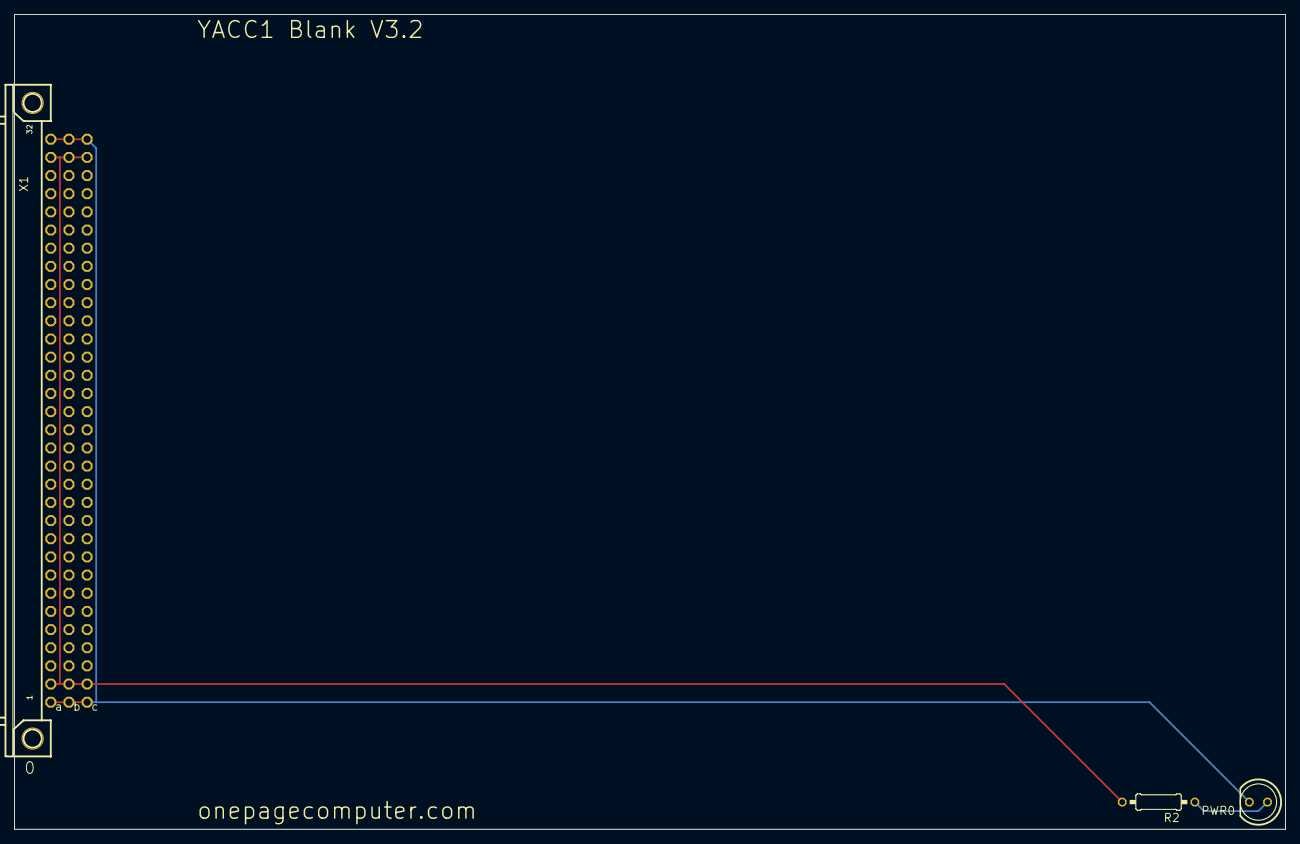
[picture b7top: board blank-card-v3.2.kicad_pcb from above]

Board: 2 copper layers, 177.8 x 114.0 mm, 3 parts (0 on the bottom side), 3 nets.
